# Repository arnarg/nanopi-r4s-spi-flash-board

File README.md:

# NanoPi R4S SPI Flash Board

A small PCB adding an SPI Flash and i2c EEPROM using the GPIO header.

In order to be low-profile enough to fit inside the metal enclosure the pin header used is [Harwin M20-7810545](https://www.harwin.com/products/M20-7810545/).

Blog post: https://codedbearder.com/posts/nanopi-r4s-spi-flash/

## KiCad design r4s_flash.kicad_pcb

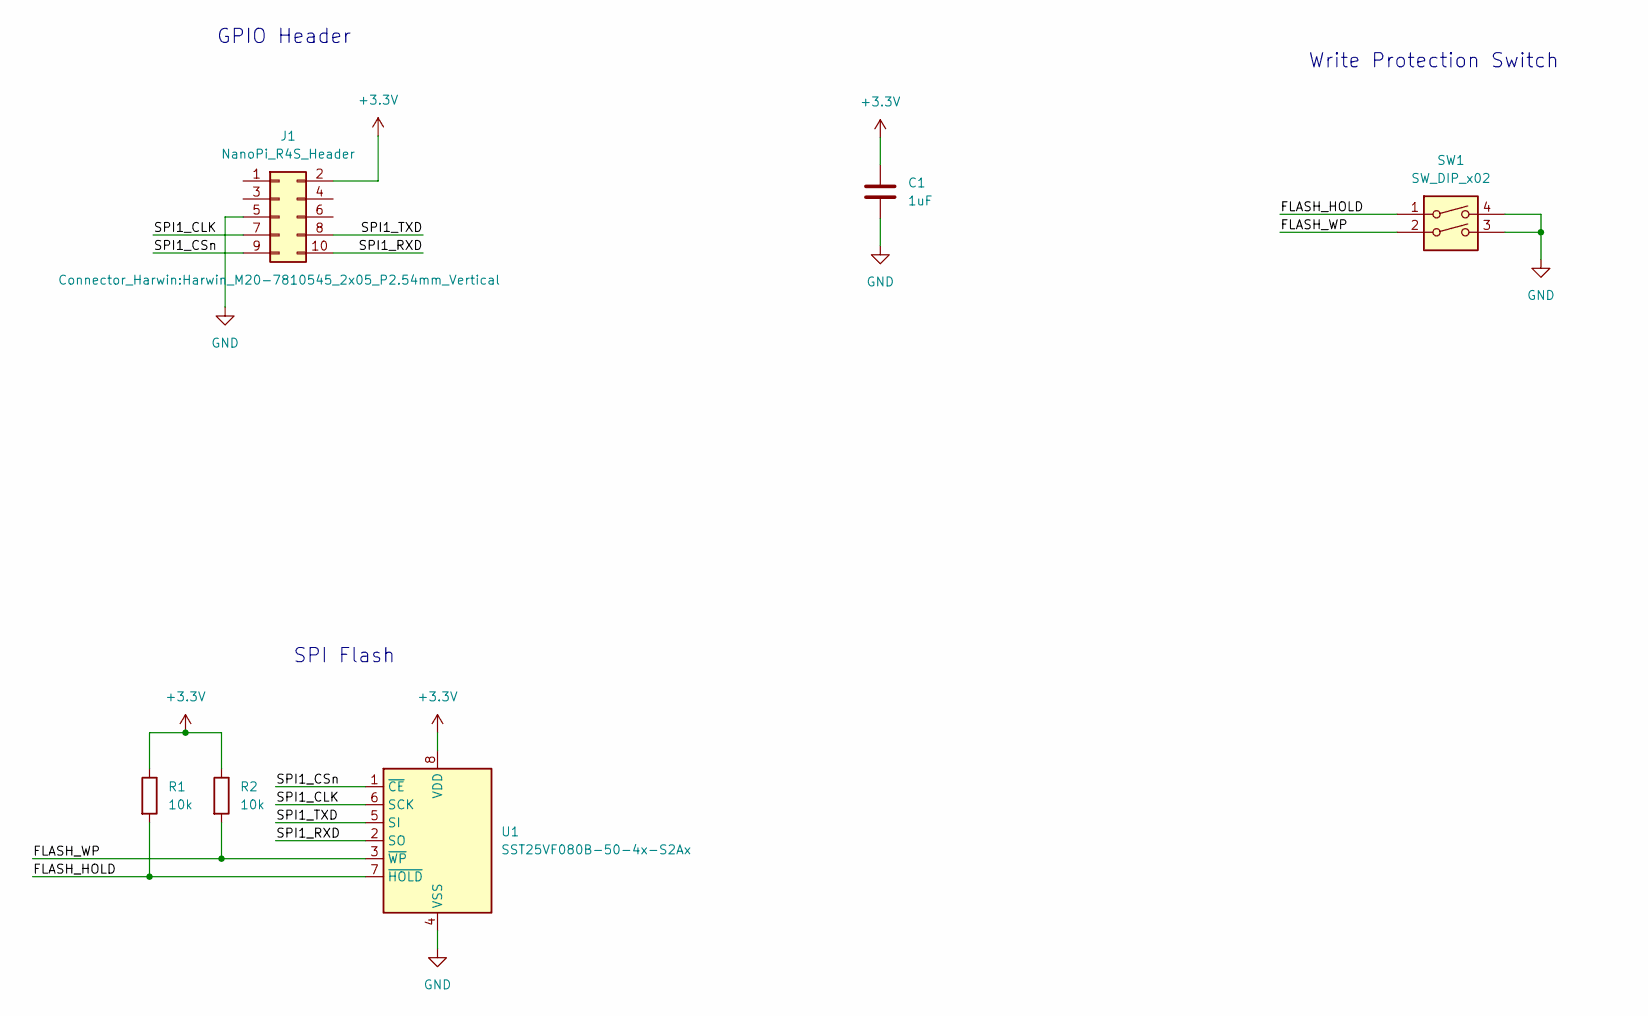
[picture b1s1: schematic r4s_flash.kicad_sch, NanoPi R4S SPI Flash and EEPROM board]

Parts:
C1: 1uF; C_0805_2012Metric_Pad1.18x1.45mm_HandSolder
J1: NanoPi_R4S_Header; Harwin_M20-7810545_2x05_P2.54mm_Vertical
R1, R2: 10k; R_0805_2012Metric_Pad1.20x1.40mm_HandSolder
SW1: SW_DIP_x02; SW_DIP_SPSTx02_Slide_Omron_A6H-2101_W6.15mm_P1.27mm
U1: SST25VF080B-50-4x-S2Ax; SOIC-8_5.275x5.275mm_P1.27mm

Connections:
+3.3V: C1.1, J1.2, R1.1, R2.1, U1.8 (VDD)
/FLASH_HOLD: R1.2, SW1.1, U1.7 (~HOLD)
/FLASH_WP: R2.2, SW1.2, U1.3 (~WP)
/SPI1_CLK: J1.7, U1.6 (SCK)
/SPI1_CSn: J1.9, U1.1 (~CE)
/SPI1_RXD: J1.10, U1.2 (SO)
/SPI1_TXD: J1.8, U1.5 (SI)
GND: C1.2, J1.5, SW1.3, SW1.4, U1.4 (VSS)

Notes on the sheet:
GPIO Header
Write Protection Switch
SPI Flash

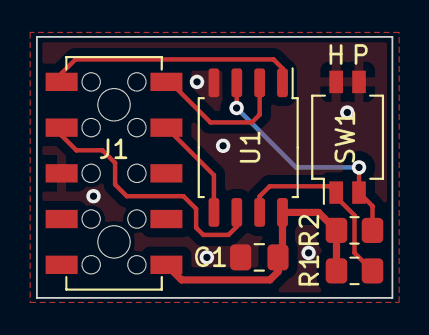
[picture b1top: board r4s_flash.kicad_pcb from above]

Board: 2 copper layers, 19.8 x 14.5 mm, 6 parts (0 on the bottom side), 8 nets.

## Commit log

2024-02-02 Add rev1.1
2024-04-04 Adding picture to README
